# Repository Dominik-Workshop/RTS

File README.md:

# RTS - Line Follower Robot

## Overview

A line follower robot built to autonomously navigate a track marked by a black line on a white surface. The goal is for the robot to complete the track as quickly as possible.

### Key Features

- **16 reflective sensors** for precise line detection
- **PD controller** for responsive steering
- **Bluetooth module** for remote control and PID parameter calibration
- **Lightweight design** at just **~70g**

## Electronics

This project features two custom-designed PCBs that are connected via a flexible flat cable (FFC):

- [**Sensor board**](/pcb/sensor_board/) - contains 16 reflective sensors for line detection

- [**Main board**](/pcb/main_board/) - responsible for the robot's core functionalities. It integrates the microcontroller, motor drivers, bluetooth module and power management circuitry

## Mechanical

The PCBs are mechanically joined with a lightweight 3D-printed connection bar. The motor and battery mounts are also 3D-printed.

### Tires

Several tire types have been tested:

- **MINI-Z Low Height Slick Tire 40° MZW39-40**: This tire provided solid grip and durability, serving as a reliable baseline for testing.
- **MINI-Z LM Wide High Grip Tire 20° MZT302-20**: This tire offered superior grip, which led to improved cornering speeds, but at the cost of durability.
- **MINI-Z RACING SLICK WIDE TYRES 20° MZW17-20B**: Initial tests showed slightly less traction, and require further testing.

## Android App

A dedicated Android app allows for remote control and tuning of the robot. Its main functions include **PID parameter calibration** and the ability to **start and stop** the robot's run.

<div align="center">
  
</div>

## Troubleshooting

<details>
<summary><b>Microcontroller doesn't program</b></summary>

Make sure that the fusebits are set as bellow:

</details>

## Used Tools

 &nbsp;&nbsp;
 &nbsp;&nbsp;
 &nbsp;&nbsp;

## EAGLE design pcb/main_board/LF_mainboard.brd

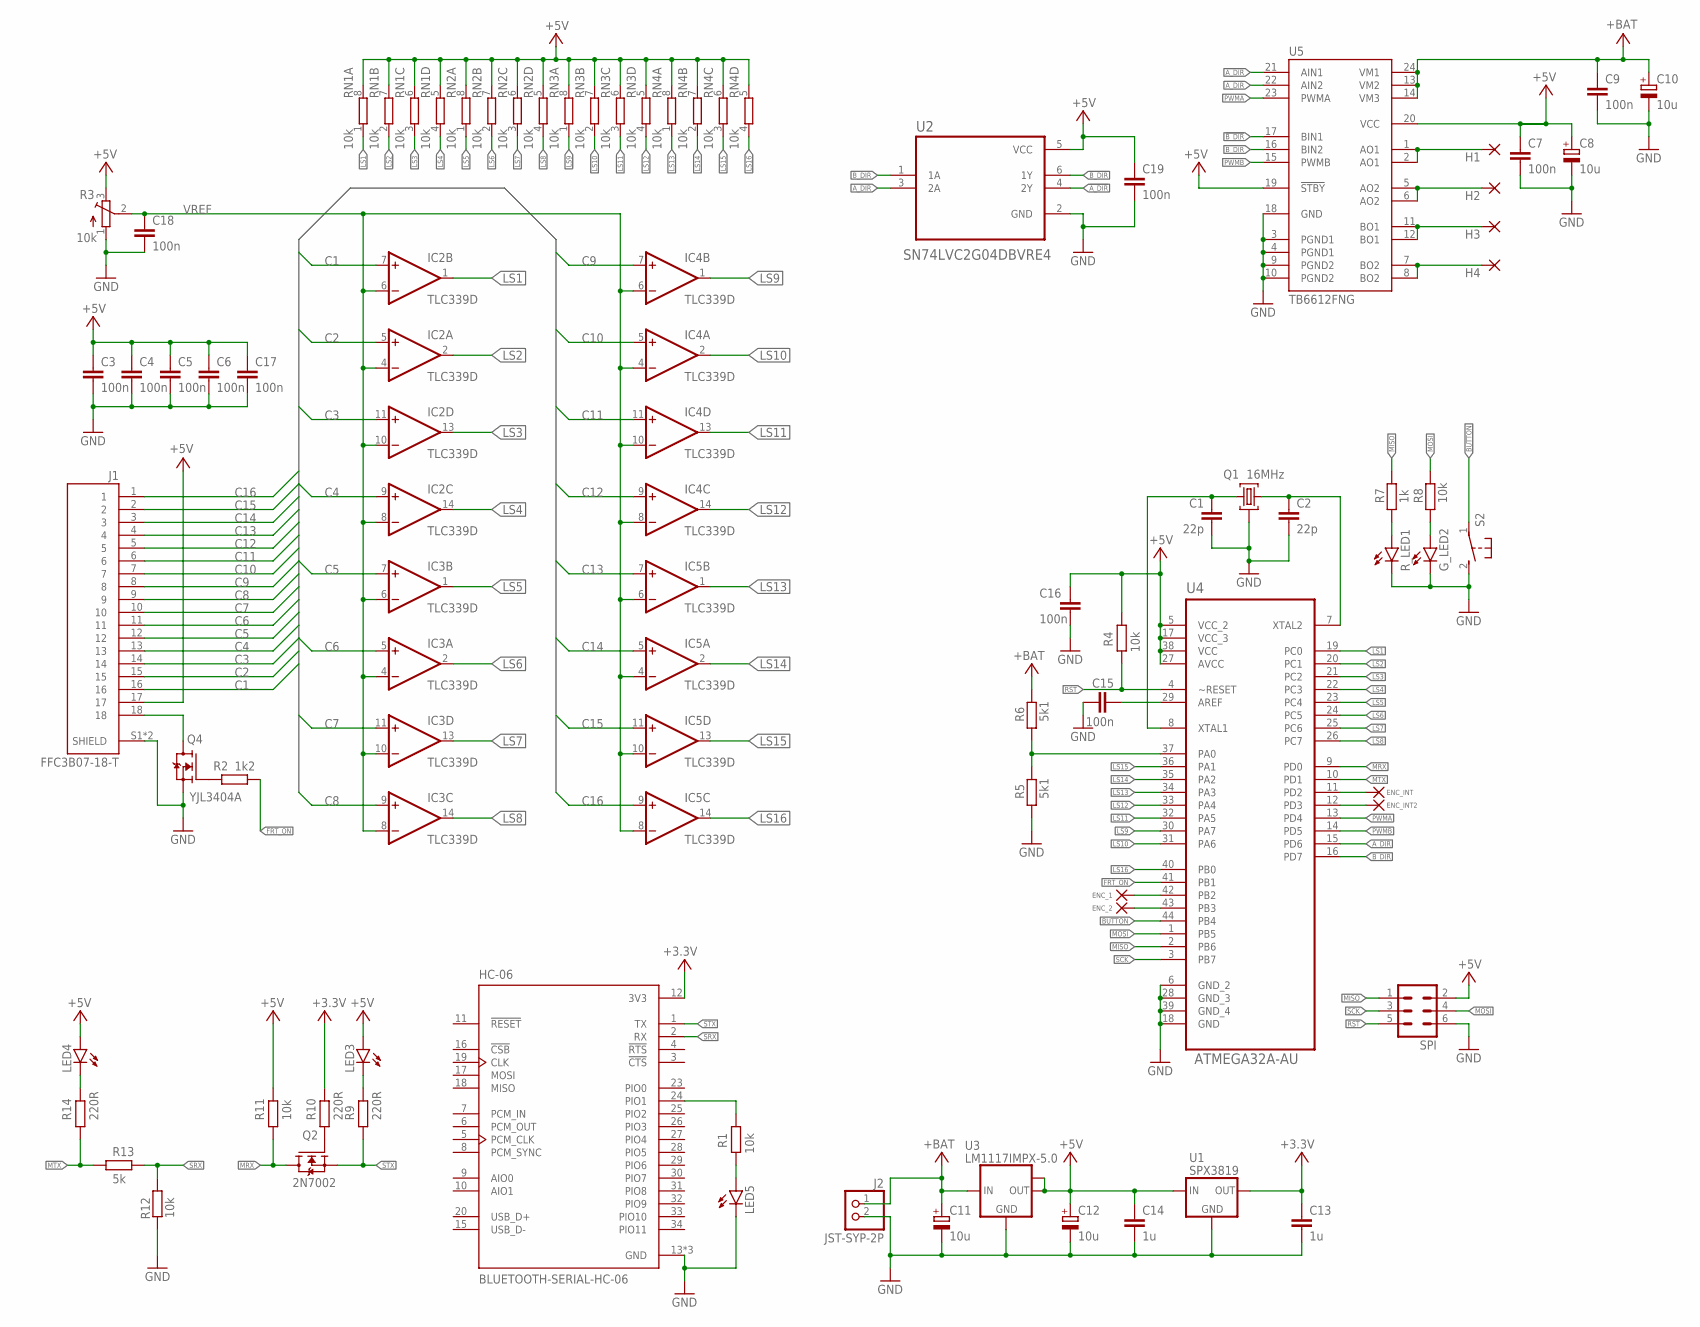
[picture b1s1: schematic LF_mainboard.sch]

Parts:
C1, C2: 22p; C0603
C3, C4, C5, C6, C7, C9, C15, C17: 100n; C0603
C8, C10, C11, C12: 10u; B/3528-21W
C13, C14: 1u; C0805
C16, C18, C19: 100n; C0402
ENC_2: 1,6/0,8
G_LED2: LEDCHIP-LED0805; CHIP-LED0805
H1, H2, H3, H4, H5, H6, H8: 1,6/0,8
HC-06: BLUETOOTH-SERIAL-HC-06; XCVR_BLUETOOTH-SERIAL-HC-06
IC2, IC3, IC4, IC5: TLC339D; SO14
J1: FFC3B07-18-T; GCT_FFC3B07-18-T
J2: JST-SYP-2P; 1X02
LED3, LED4, LED5: LEDCHIP-LED0805; CHIP-LED0805
Q1: 16MHz; CRYSTAL_3,4X2,7
Q2: 2N7002; SOT95P240X111-3N
Q4: YJL3404A; SOT95P240X111-3N
R1: 10k; R0603
R2: 1k2; R0603
R3: 10k; SM-42/43A
R4, R8, R11, R12: 10k; R0402
R5, R6: 5k1; R0603
R7: 1k; R0402
R9, R10, R14: 220R; R0402
R13: 5k; R0402
RN1, RN2, RN3, RN4: 10k; CAT16
R_LED1: LEDCHIP-LED0805; CHIP-LED0805
S2: DTSM-3
SPI: MA03-2
U1: SPX3819; SOT23-5
U2: SN74LVC2G04DBVRE4; SOT95P280X145-6N
U3: LM1117IMPX-5.0; SOT223
U4: ATMEGA32A-AU; QFP80P1200X1200X120-44N
U5: TB6612FNG; SSOP24

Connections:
!A_DIR: U2.4 (2Y), U5.21 (AIN1)
!B_DIR: U2.6 (1Y), U5.17 (BIN1)
+3.3V: C13.1, HC-06.12 (3V3), R10.2, U1.5 (OUT)
+5V: C3.1, C4.1, C5.1, C6.1, C7.1, C8.+, C12.+, C14.1, C16.1, C17.1, C19.1, IC2.3 (V+), IC3.3 (V+), IC4.3 (V+), IC5.3 (V+), J1.17, LED3.A, LED4.A, R3.3 (E), R4.2, R11.2, RN1.5 (2), RN1.6 (2), RN1.7 (2), RN1.8 (2), RN2.5 (2), RN2.6 (2), RN2.7 (2), RN2.8 (2), RN3.5 (2), RN3.6 (2), RN3.7 (2), RN3.8 (2), RN4.5 (2), RN4.6 (2), RN4.7 (2), RN4.8 (2), SPI.2, U1.1 (IN), U1.3 (IN), U2.5 (VCC), U3.2 (OUT), U3.TAB (OUT1), U4.5 (VCC_2), U4.17 (VCC_3), U4.27 (AVCC), U4.38 (VCC), U5.19 (!STBY), U5.20 (VCC)
+BAT: C9.1, C10.+, C11.+, J2.1, R6.2, U3.3 (IN), U5.13 (VM2), U5.14 (VM3), U5.24 (VM1)
AO: H1.1, U5.1 (AO1), U5.2 (AO1)
AO2: H2.1, U5.5 (AO2), U5.6 (AO2)
AREF: C15.2, U4.29 (AREF)
A_DIR: U2.3 (2A), U4.15 (PD6), U5.22 (AIN2)
BAT_MEAS: R5.2, R6.1, U4.37 (PA0)
BO1: H3.1, U5.11 (BO1), U5.12 (BO1)
BO2: H4.1, U5.7 (BO2), U5.8 (BO2)
BUTTON: S2.1, U4.44 (PB4)
B_DIR: U2.1 (1A), U4.16 (PD7), U5.16 (BIN2)
C1: IC2.7 (+IN), J1.16
C2: IC2.5 (+IN), J1.15
C3: IC2.11 (+IN), J1.14
C4: IC2.9 (+IN), J1.13
C5: IC3.7 (+IN), J1.12
C6: IC3.5 (+IN), J1.11
C7: IC3.11 (+IN), J1.10
C8: IC3.9 (+IN), J1.9
C9: IC4.7 (+IN), J1.8
C10: IC4.5 (+IN), J1.7
C11: IC4.11 (+IN), J1.6
C12: IC4.9 (+IN), J1.5
C13: IC5.7 (+IN), J1.4
C14: IC5.5 (+IN), J1.3
C15: IC5.11 (+IN), J1.2
C16: IC5.9 (+IN), J1.1
ENC_1: H8.1, U4.42 (PB2)
ENC_2: ENC_2.1, U4.43 (PB3)
ENC_INT: H5.1, U4.11 (PD2)
ENC_INT2: H6.1, U4.12 (PD3)
FRT_ON: R2.1, U4.41 (PB1)
GND: C1.2, C2.2, C3.2, C4.2, C5.2, C6.2, C7.2, C8.-, C9.2, C10.-, C11.-, C12.-, C13.2, C14.2, C15.1, C16.2, C17.2, C18.2, C19.2, G_LED2.C, HC-06.13 (GND), HC-06.21 (GND), HC-06.22 (GND), IC2.12 (V-), IC3.12 (V-), IC4.12 (V-), IC5.12 (V-), J1.S1 (SHIELD), J1.S2 (SHIELD), J2.2, LED5.C, Q1.GND (2), Q1.GND2 (2), Q4.2 (S), R3.1 (A), R5.1, R12.2, R_LED1.C, S2.2, SPI.6, U1.2 (GND), U2.2 (GND), U3.1 (GND), U4.6 (GND_2), U4.18 (GND), U4.28 (GND_3), U4.39 (GND_4), U5.3 (PGND1), U5.4 (PGND1), U5.9 (PGND2), U5.10 (PGND2), U5.18 (GND)
LED1: R7.1, R_LED1.A
LED2: G_LED2.A, R8.1
LS1: IC2.1 (OUT), RN1.1, U4.19 (PC0)
LS2: IC2.2 (OUT), RN1.2 (1), U4.20 (PC1)
LS3: IC2.13 (OUT), RN1.3 (1), U4.21 (PC2)
LS4: IC2.14 (OUT), RN1.4 (1), U4.22 (PC3)
LS5: IC3.1 (OUT), RN2.1, U4.23 (PC4)
LS6: IC3.2 (OUT), RN2.2 (1), U4.24 (PC5)
LS7: IC3.13 (OUT), RN2.3 (1), U4.25 (PC6)
LS8: IC3.14 (OUT), RN2.4 (1), U4.26 (PC7)
LS9: IC4.1 (OUT), RN3.1, U4.30 (PA7)
LS10: IC4.2 (OUT), RN3.2 (1), U4.31 (PA6)
LS11: IC4.13 (OUT), RN3.3 (1), U4.32 (PA5)
LS12: IC4.14 (OUT), RN3.4 (1), U4.33 (PA4)
LS13: IC5.1 (OUT), RN4.1, U4.34 (PA3)
LS14: IC5.2 (OUT), RN4.2 (1), U4.35 (PA2)
LS15: IC5.13 (OUT), RN4.3 (1), U4.36 (PA1)
LS16: IC5.14 (OUT), RN4.4 (1), U4.40 (PB0)
MISO: R7.2, SPI.1, U4.2 (PB6)
MOSI: R8.2, SPI.4, U4.1 (PB5)
MRX: Q2.3 (D), R11.1, U4.9 (PD0)
MTX: R13.1, R14.1, U4.10 (PD1)
unnamed: C1.1, Q1.CRST1 (1), U4.8 (XTAL1)
unnamed: C2.1, Q1.CRST2 (3), U4.7 (XTAL2)
unnamed: J1.18, Q4.3 (D)
unnamed: Q4.1 (G), R2.2
unnamed: HC-06.24 (PIO1), R1.2
unnamed: Q2.1 (G), R10.1
unnamed: LED4.C, R14.2
unnamed: LED3.C, R9.2
unnamed: LED5.A, R1.1
PWMA: U4.13 (PD4), U5.23 (PWMA)
PWMB: U4.14 (PD5), U5.15 (PWMB)
RST: R4.1, SPI.5, U4.4 (~RESET)
SCK: SPI.3, U4.3 (PB7)
SRX: HC-06.2 (RX), R12.1, R13.2
STX: HC-06.1 (TX), Q2.2 (S), R9.1
VREF: C18.1, IC2.4 (-IN), IC2.6 (-IN), IC2.8 (-IN), IC2.10 (-IN), IC3.4 (-IN), IC3.6 (-IN), IC3.8 (-IN), IC3.10 (-IN), IC4.4 (-IN), IC4.6 (-IN), IC4.8 (-IN), IC4.10 (-IN), IC5.4 (-IN), IC5.6 (-IN), IC5.8 (-IN), IC5.10 (-IN), R3.2 (S)

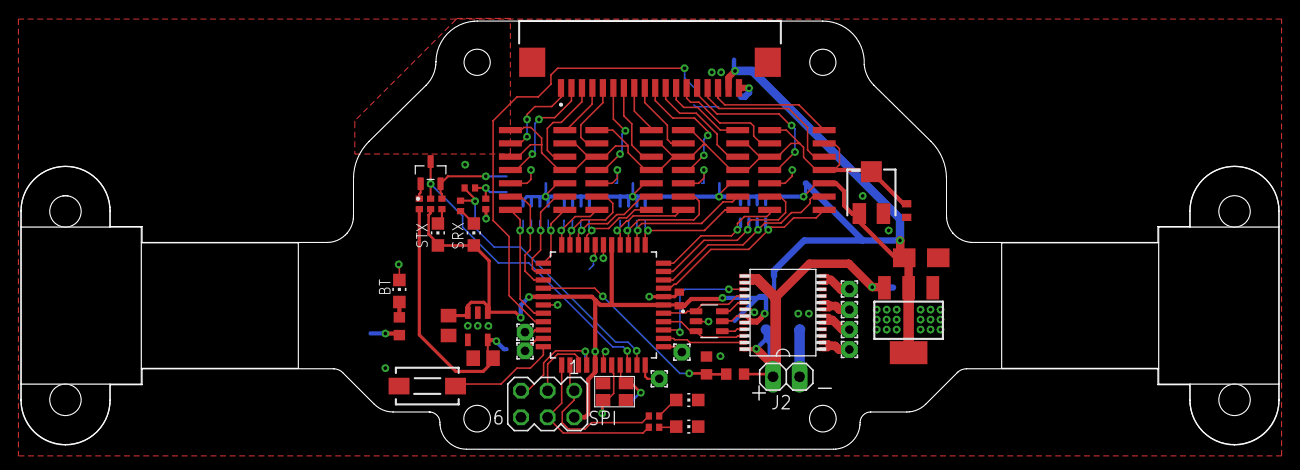
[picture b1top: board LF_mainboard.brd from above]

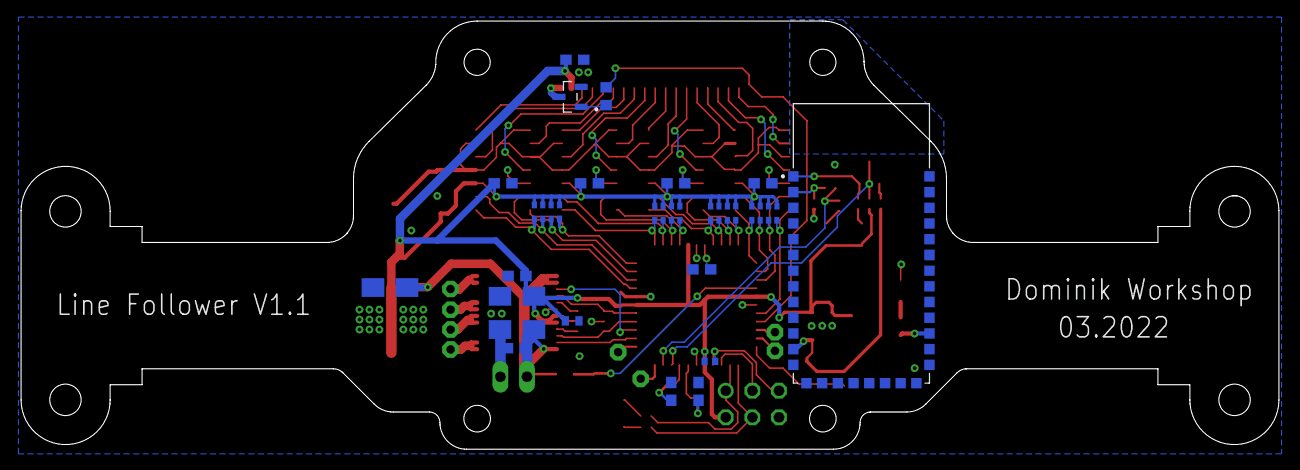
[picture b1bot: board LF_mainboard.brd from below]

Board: 2 copper layers, 120.1 x 40.9 mm, 69 parts (22 on the bottom side), 74 nets.

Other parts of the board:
U$1, U$2: HP_NM

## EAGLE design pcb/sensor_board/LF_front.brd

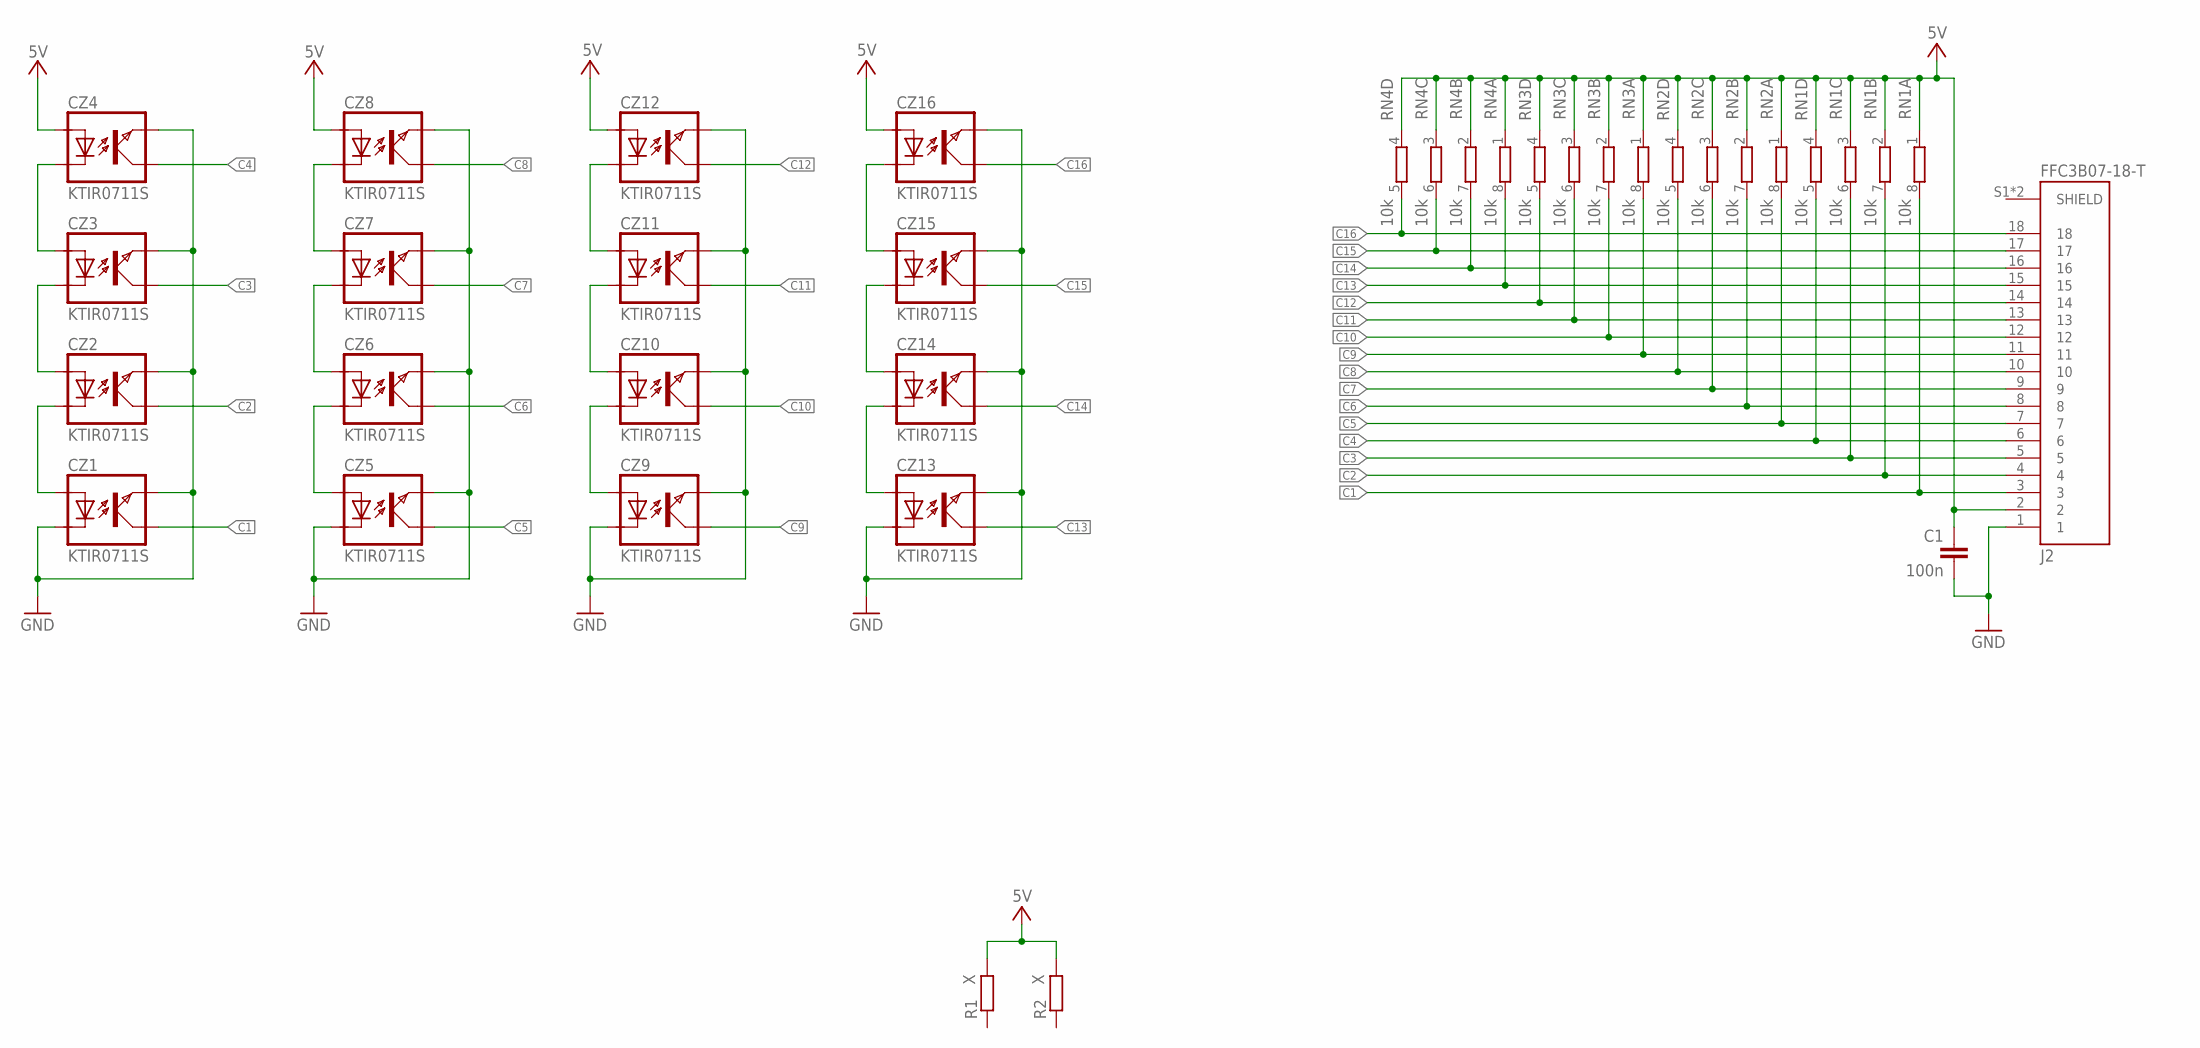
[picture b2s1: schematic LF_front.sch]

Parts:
C1: 100n; C0402
CZ1, CZ2, CZ3, CZ4, CZ5, CZ6, CZ7, CZ8, CZ9, CZ10, CZ11, CZ12, CZ13, CZ14, CZ15, CZ16: KTIR0711S; TOP
J2: FFC3B07-18-T; GCT_FFC3B07-18-T
R1, R2: X; 0207/7
RN1, RN2, RN3, RN4: 10k; EXB38V

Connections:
5V: C1.2, CZ4.ANODA, CZ8.ANODA, CZ12.ANODA, CZ16.ANODA, J2.2, R1.2, R2.2, RN1.1, RN1.2 (1), RN1.3 (1), RN1.4 (1), RN2.1, RN2.2 (1), RN2.3 (1), RN2.4 (1), RN3.1, RN3.2 (1), RN3.3 (1), RN3.4 (1), RN4.1, RN4.2 (1), RN4.3 (1), RN4.4 (1)
C1: CZ1.KOLEKTOR, J2.3, RN1.8 (2)
C2: CZ2.KOLEKTOR, J2.4, RN1.7 (2)
C3: CZ3.KOLEKTOR, J2.5, RN1.6 (2)
C4: CZ4.KOLEKTOR, J2.6, RN1.5 (2)
C5: CZ5.KOLEKTOR, J2.7, RN2.8 (2)
C6: CZ6.KOLEKTOR, J2.8, RN2.7 (2)
C7: CZ7.KOLEKTOR, J2.9, RN2.6 (2)
C8: CZ8.KOLEKTOR, J2.10, RN2.5 (2)
C9: CZ9.KOLEKTOR, J2.11, RN3.8 (2)
C10: CZ10.KOLEKTOR, J2.12, RN3.7 (2)
C11: CZ11.KOLEKTOR, J2.13, RN3.6 (2)
C12: CZ12.KOLEKTOR, J2.14, RN3.5 (2)
C13: CZ13.KOLEKTOR, J2.15, RN4.8 (2)
C14: CZ14.KOLEKTOR, J2.16, RN4.7 (2)
C15: CZ15.KOLEKTOR, J2.17, RN4.6 (2)
C16: CZ16.KOLEKTOR, J2.18, RN4.5 (2)
GND: C1.1, CZ1.EMITER, CZ1.KATODA, CZ2.EMITER, CZ3.EMITER, CZ4.EMITER, CZ5.EMITER, CZ5.KATODA, CZ6.EMITER, CZ7.EMITER, CZ8.EMITER, CZ9.EMITER, CZ9.KATODA, CZ10.EMITER, CZ11.EMITER, CZ12.EMITER, CZ13.EMITER, CZ13.KATODA, CZ14.EMITER, CZ15.EMITER, CZ16.EMITER, J2.1
unnamed: CZ1.ANODA, CZ2.KATODA
unnamed: CZ2.ANODA, CZ3.KATODA
unnamed: CZ3.ANODA, CZ4.KATODA
unnamed: CZ15.ANODA, CZ16.KATODA
unnamed: CZ14.ANODA, CZ15.KATODA
unnamed: CZ13.ANODA, CZ14.KATODA
unnamed: CZ11.ANODA, CZ12.KATODA
unnamed: CZ10.ANODA, CZ11.KATODA
unnamed: CZ9.ANODA, CZ10.KATODA
unnamed: CZ5.ANODA, CZ6.KATODA
unnamed: CZ6.ANODA, CZ7.KATODA
unnamed: CZ7.ANODA, CZ8.KATODA

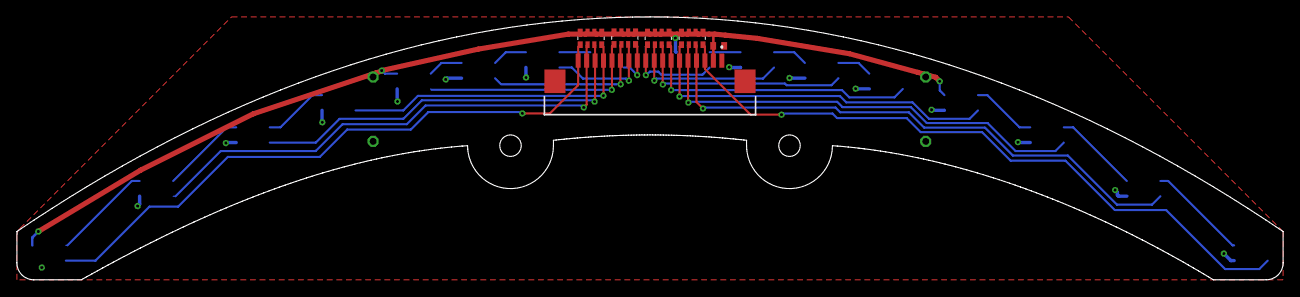
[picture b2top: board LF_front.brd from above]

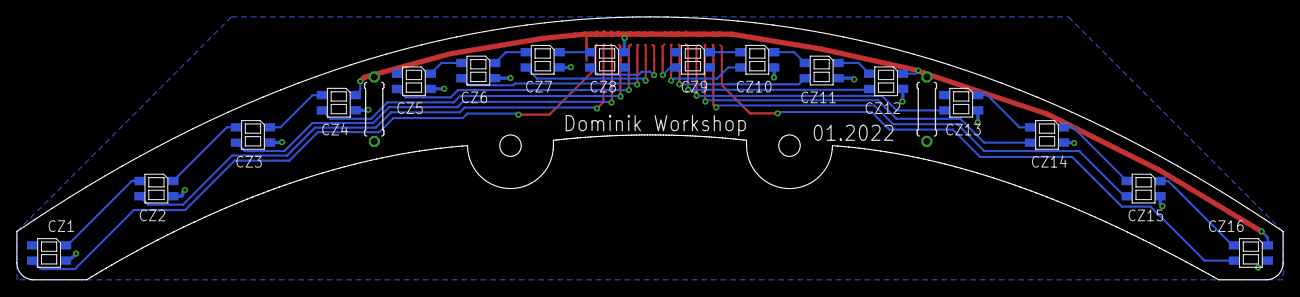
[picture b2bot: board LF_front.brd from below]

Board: 2 copper layers, 149.8 x 31.1 mm, 24 parts (18 on the bottom side), 30 nets.

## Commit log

2024-07-01 init
2024-07-05 add basic description
2024-07-05 decrease spacing between logos
2024-07-05 align app screenshots
2024-11-17 Space out app screenshots in README
2025-04-06 Add information about used tires to README
2025-08-07 Improve README
